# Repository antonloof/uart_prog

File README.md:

# uart_prog
a usb2uart programmer for esp32

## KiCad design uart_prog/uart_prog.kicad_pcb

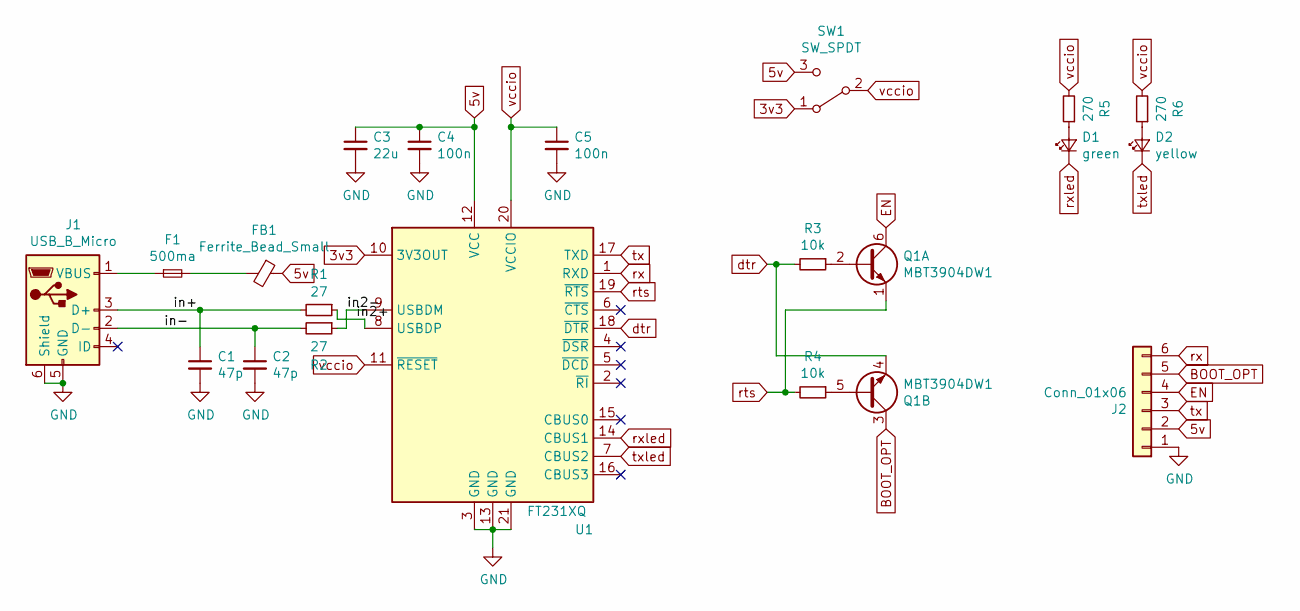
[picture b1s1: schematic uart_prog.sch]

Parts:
C1, C2: 47p; C_0603_1608Metric_Pad1.05x0.95mm_HandSolder
C3: 22u; C_0805_2012Metric_Pad1.18x1.45mm_HandSolder
C4, C5: 100n; C_0603_1608Metric_Pad1.05x0.95mm_HandSolder
D1: green; LED_0805_2012Metric_Pad1.15x1.40mm_HandSolder
D2: yellow; LED_0805_2012Metric_Pad1.15x1.40mm_HandSolder
F1: 500ma; Fuse_0805_2012Metric_Pad1.15x1.40mm_HandSolder
FB1: Ferrite_Bead_Small; L_0805_2012Metric_Pad1.15x1.40mm_HandSolder
J1: USB_B_Micro; USB_MICRO_10118193-0001LF
J2: Conn_01x06; PinHeader_1x06_P2.54mm_Horizontal
Q1: MBT3904DW1; SOT-363_SC-70-6
R1, R2: 27; R_0603_1608Metric_Pad1.05x0.95mm_HandSolder
R3, R4: 10k; R_0603_1608Metric_Pad1.05x0.95mm_HandSolder
R5, R6: 270; R_0805_2012Metric_Pad1.15x1.40mm_HandSolder
SW1: SW_SPDT; PinHeader_1x03_P2.54mm_Vertical
U1: FT231XQ; QFN-20-1EP_4x4mm_P0.5mm_EP2.5x2.5mm

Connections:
3v3: SW1.1 (A), U1.10 (3V3OUT)
5v: C3.1, C4.1, FB1.1, J2.2, SW1.3 (C), U1.12 (VCC)
/in2+: R1.1, U1.8 (USBDP)
/in2-: R2.1, U1.9 (USBDM)
/in+: C1.1, J1.3 (D+), R1.2
/in-: C2.1, J1.2 (D-), R2.2
BOOT_OPT: J2.5, Q1.3 (C2)
EN: J2.4, Q1.6 (C1)
GND: C1.2, C2.2, C3.2, C4.2, C5.2, J1.5 (GND), J1.6 (Shield), J2.1, U1.3 (GND), U1.13 (GND), U1.21 (GND)
unnamed: D1.2 (A), R5.1
unnamed: D2.2 (A), R6.1
unnamed: F1.1, J1.1 (VBUS)
unnamed: F1.2, FB1.2
unnamed: Q1.2 (B1), R3.1
unnamed: Q1.5 (B2), R4.1
dtr: Q1.4 (E2), R3.2, U1.18 (~DTR)
rts: Q1.1 (E1), R4.2, U1.19 (~RTS)
rx: J2.6, U1.1 (RXD)
rxled: D1.1 (K), U1.14 (CBUS1)
tx: J2.3, U1.17 (TXD)
txled: D2.1 (K), U1.7 (CBUS2)
vccio: C5.1, R5.2, R6.2, SW1.2 (B), U1.11 (~RESET), U1.20 (VCCIO)

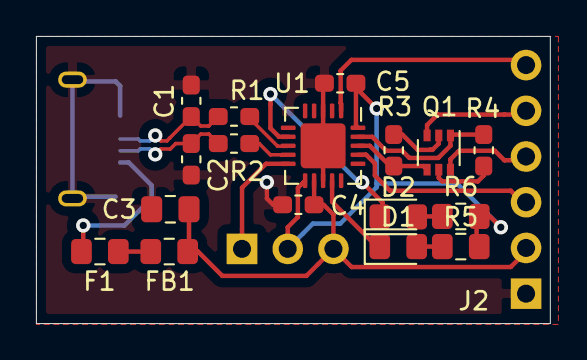
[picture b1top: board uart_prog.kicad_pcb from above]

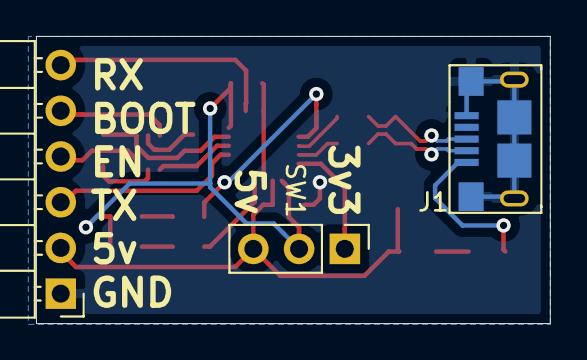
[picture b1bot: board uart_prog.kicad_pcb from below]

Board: 2 copper layers, 28.6 x 16.0 mm, 20 parts (3 on the bottom side), 22 nets.

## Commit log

2021-05-03 Add kicad
2021-05-03 Add pcb
2021-05-03 Layout doner
2021-05-03 Pcb rev1
2021-11-18 Add schematic back again ...
2021-11-18 Updata schema to reflect board rev2
2021-11-20 rename en to reset
